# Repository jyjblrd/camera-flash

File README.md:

# camera-flash
 A compact 3d printed camera flash

Check out my blog post for more details: [https://joshuabird.com/blog/post/making-a-compact-camera-flash](https://joshuabird.com/blog/post/making-a-compact-camera-flash)

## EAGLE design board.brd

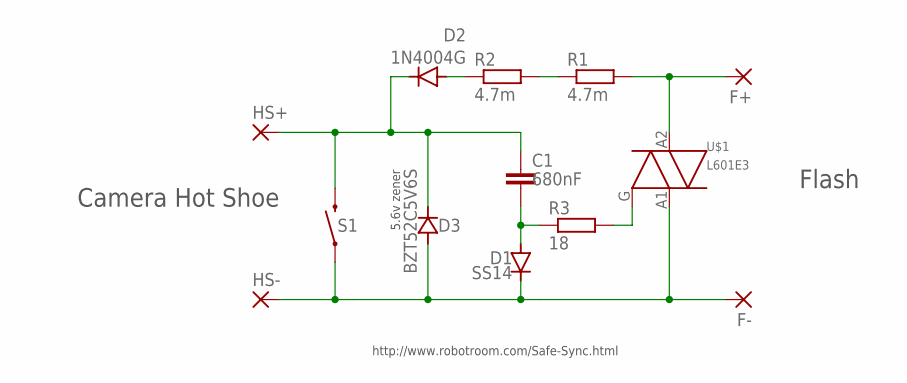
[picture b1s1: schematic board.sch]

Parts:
C1: 680nF; C0603
D1: SS14; DO214AC
D2: 1N4004G; DO214AC
D3: BZT52C5V6S; SOD323
F+: 1,6/0,8
F-: 1,6/0,8
HS+: 1,6/0,8
HS-: 1,6/0,8
R1, R2: 4.7m; R0603
R3: 18; R0603
S1: MOMENTARY-SWITCH-SPST-SMD-6.0X3.5MM; TACTILE_SWITCH_SMD_6.0X3.5MM
U$1: L601E3; TO92E

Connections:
unnamed: R1.1, R2.2
unnamed: F+.1, R1.2, U$1.A2
unnamed: D1.C, D3.2 (A), F-.1, HS-.1, S1.1, U$1.A1
unnamed: R3.2, U$1.G
unnamed: C1.2, D1.A, R3.1
unnamed: C1.1, D2.C, D3.1 (C), HS+.1, S1.2
unnamed: D2.A, R2.1

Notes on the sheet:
5.6v zener
http://www.robotroom.com/Safe-Sync.html
Camera Hot Shoe
Flash

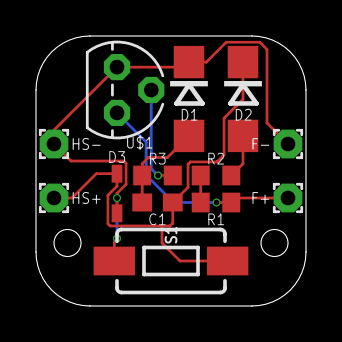
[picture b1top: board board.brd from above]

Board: 2 copper layers, 15.0 x 15.0 mm, 13 parts (0 on the bottom side), 7 nets.

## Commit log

2021-07-30 init
2021-07-30 step & img

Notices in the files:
parts and their libraries:
SparkFun-Switches: Licensing: Creative Commons ShareAlike 4.0 International - https://creativecommons.org/licenses/by-sa/4.0
